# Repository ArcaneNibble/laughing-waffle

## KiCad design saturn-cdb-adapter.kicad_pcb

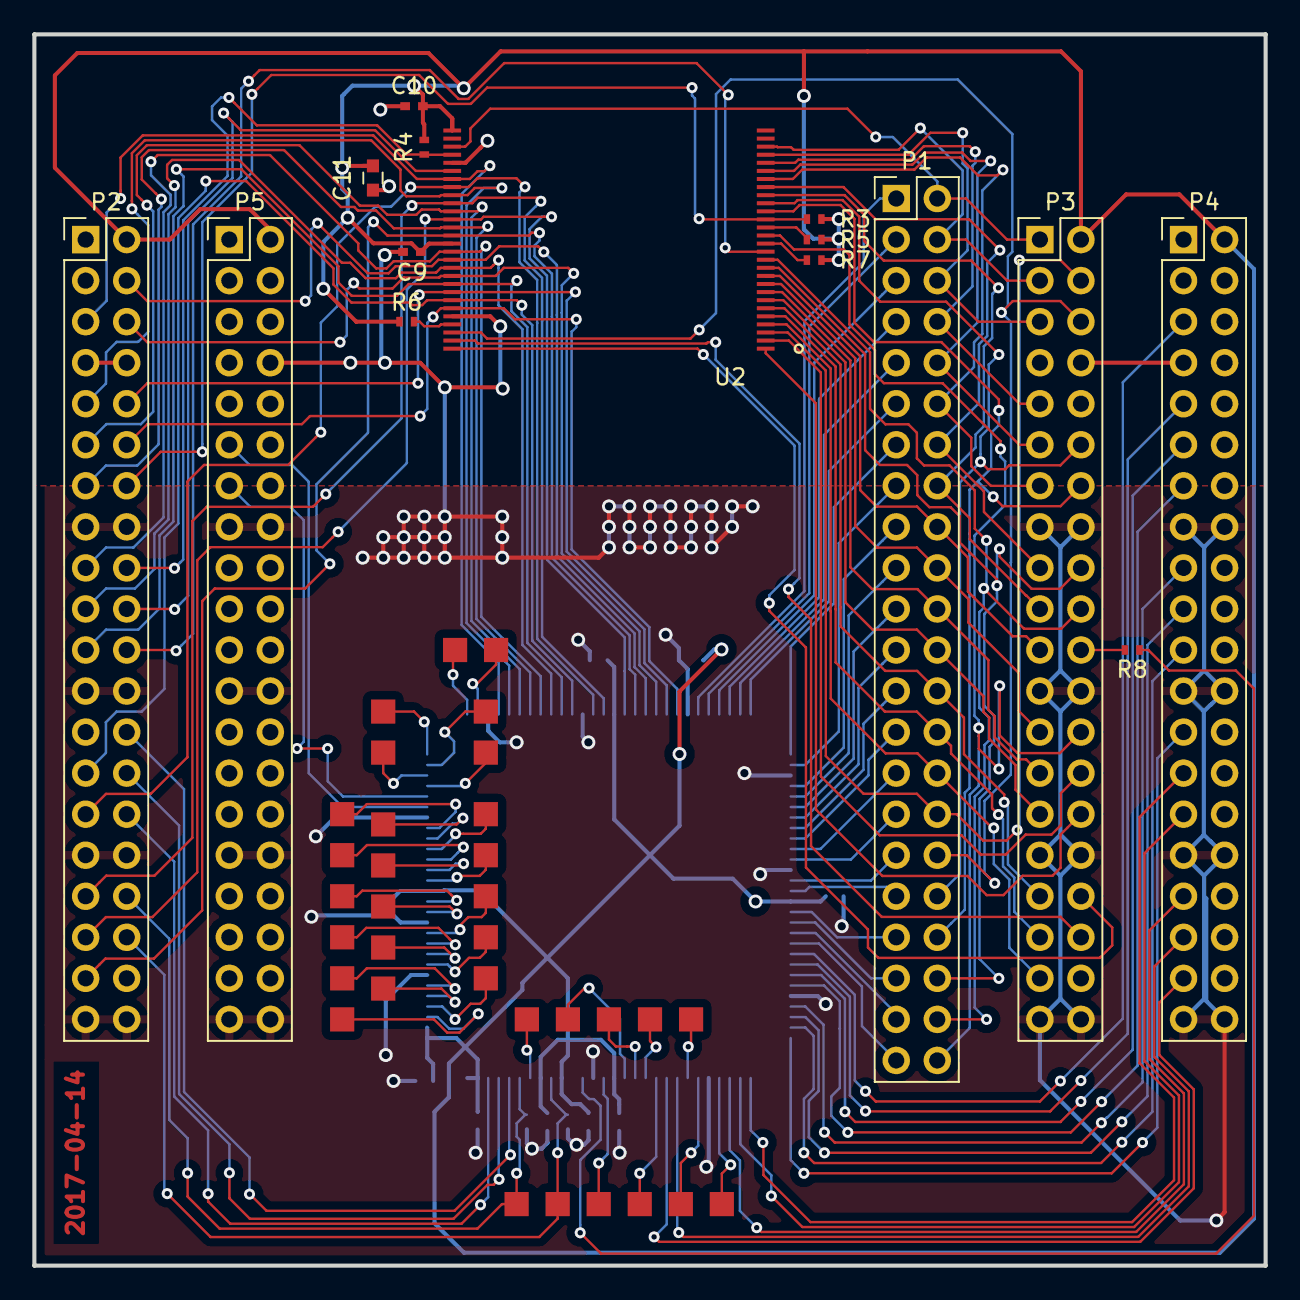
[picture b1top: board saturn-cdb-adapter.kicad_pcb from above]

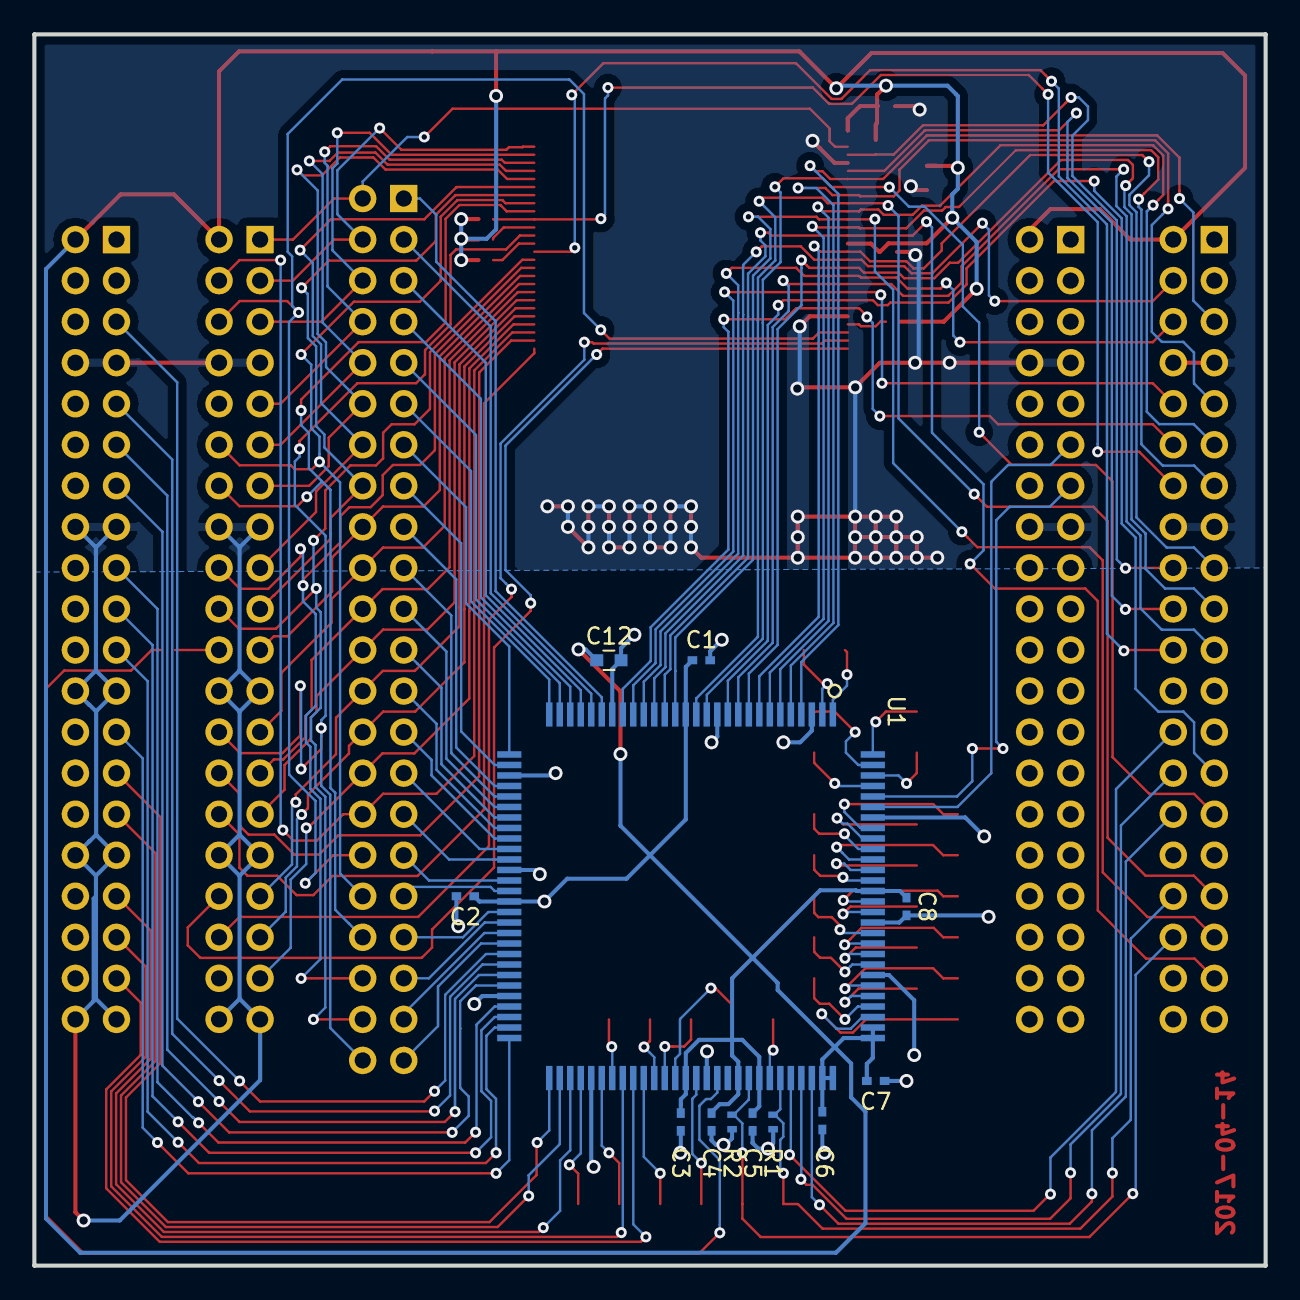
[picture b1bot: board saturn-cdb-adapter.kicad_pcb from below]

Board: 2 copper layers, 76.2 x 76.2 mm, 60 parts (12 on the bottom side), 126 nets.

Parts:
C1, C2, C3, C4, C5, C6, C7, C8, C9, C10: 0.1uF; C_0402_NoSilk
C11, C12: 1uF; C_0603
P1: CONN_02X22; Pin_Header_Straight_2x22_Pitch2.54mm
P2, P3, P4, P5: CONN_02X20; Pin_Header_Straight_2x20_Pitch2.54mm
R1, R2, R3, R4: 10k; R_0402_NoSilk
R5, R6, R7, R8: 0; R_0402_NoSilk
U1: SH1; cdb-sh1
U2: MT28EW_FLASH; TSOP56
W1, W2, W3, W4, W5, W6, W7, W8, W9, W10, W11, W12, W13, W14, W15, W16, W17, W18, W19, W20, W21, W22, W23, W24, W25, W26, W27, W28, W29, W30, W31, W32, W33: TEST_1P; Measurement_Point_Square-SMD-Pad_Small

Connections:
+3V3: C1.1, C2.1, C3.1, C4.1, C5.1, C6.1, C7.1, C8.1, C9.1, C10.1, C11.1, C12.1, P2.2, P3.2, P4.2, P5.2, R3.1, R4.1, R5.1, R6.1, R7.1, U1.15, U1.43, U1.70, U1.75, U1.77, U1.83, U1.84, U1.85, U1.86, U1.99, U2.29, U2.43
/Flash and CPU/CPU_A0: P1.1, U1.23
/Flash and CPU/CPU_A1: P1.3, U1.24
/Flash and CPU/CPU_A2: P1.5, U1.25
/Flash and CPU/CPU_A3: P1.7, U1.26
/Flash and CPU/CPU_A4: P1.9, U1.27
/Flash and CPU/CPU_A5: P1.11, U1.28
/Flash and CPU/CPU_A6: P1.13, U1.29
/Flash and CPU/CPU_A7: P1.15, U1.30
/Flash and CPU/CPU_A8: P1.17, U1.32
/Flash and CPU/CPU_A9: P1.19, U1.33
/Flash and CPU/CPU_A10: P1.21, U1.34
/Flash and CPU/CPU_A11: P1.23, U1.35
/Flash and CPU/CPU_A12: P1.25, U1.36
/Flash and CPU/CPU_A13: P1.27, U1.37
/Flash and CPU/CPU_A14: P1.29, U1.38
/Flash and CPU/CPU_A15: P1.31, U1.39
/Flash and CPU/CPU_A16: P1.33, U1.41
/Flash and CPU/CPU_A17: P1.35, U1.42
/Flash and CPU/CPU_A18: P1.37, U1.44
/Flash and CPU/CPU_A19: P1.39, U1.45
/Flash and CPU/CPU_A20: P1.41, U1.46
/Flash and CPU/CPU_A21: P1.43, U1.47
AD0: P2.5, U1.4, U2.35
AD1: P2.9, U1.5, U2.37
AD2: P2.11, U1.6, U2.39
AD3: P2.13, U1.7, U2.41
AD4: P2.17, U1.8, U2.44
AD5: P2.19, U1.9, U2.46
AD6: P2.21, U1.10, U2.48
AD7: P2.27, U1.11, U2.50
AD8: P2.29, U1.13, U2.36
AD9: P2.33, U1.14, U2.38
AD10: P2.35, U1.16, U2.40
AD11: P2.37, U1.17, U2.42
AD12: P2.4, U1.18, U2.45
AD13: P2.6, U1.19, U2.47
AD14: P2.10, U1.20, U2.49
AD15: P2.12, U1.21, U2.51
CPU_CLK: R8.1, U1.73
CPU_DPH: P4.37, U1.65
CPU_DPL: P4.35, U1.64
CPU_NMI: P2.36, R2.1, U1.76, W2.1
CPU_RX: P5.11, U1.107
CPU_TX: P5.13, U1.108
CPU_~CS0: P4.5, U1.48
CPU_~CS1: P4.9, U1.49
CPU_~CS2: P4.11, U1.50
CPU_~CS3: P4.13, U1.51
CPU_~CS4: P4.17, U1.53
CPU_~CS5: P4.19, U1.54
CPU_~CS6: P4.21, U1.55
CPU_~CS7: P4.25, U1.56
CPU_~RD: P4.33, U1.59
CPU_~RES: P2.34, R1.1, U1.79, W1.1
CPU_~WRH~/~LBS~: P4.29, U1.58
CPU_~WRL~/~WR: P4.27, U1.57
FLASH_A0: P1.2, P3.1, U2.31
FLASH_A1: P1.4, P3.3, U2.26
FLASH_A2: P1.6, P3.5, U2.25
FLASH_A3: P1.8, P3.9, U2.24
FLASH_A4: P1.10, P3.11, U2.23
FLASH_A5: P1.12, P3.13, U2.22
FLASH_A6: P1.14, P3.17, U2.21
FLASH_A7: P1.16, P3.19, U2.20
FLASH_A8: P1.18, P3.21, U2.10
FLASH_A9: P1.20, P3.25, U2.9
FLASH_A10: P1.22, P3.27, U2.8
FLASH_A11: P1.24, P3.29, U2.7
FLASH_A12: P1.26, P3.33, U2.6
FLASH_A13: P1.28, P3.35, U2.5
FLASH_A14: P1.30, P3.37, U2.4
FLASH_A15: P1.32, P3.4, U2.3
FLASH_A16: P1.34, P3.6, U2.54
FLASH_A17: P1.36, P3.12, U2.19
FLASH_A18: P1.38, P3.14, U2.18
FLASH_A19: P1.40, P3.18, U2.11
FLASH_A20: P1.42, P3.20, U2.12
FLASH_A21: P1.44, P3.26, U2.15
FLASH_A22: P3.28, U2.2
FLASH_A23: P3.30, U2.1
FLASH_A24: P3.34, U2.56
FLASH_A25: P3.36, U2.55
FLASH_READY: P2.14, R3.2, U2.17
GND: C1.2, C2.2, C3.2, C4.2, C5.2, C6.2, C7.2, C8.2, C9.2, C10.2, C11.2, C12.2, P2.7, P2.8, P2.15, P2.16, P2.23, P2.24, P2.31, P2.32, P2.39, P2.40, P3.7, P3.8, P3.15, P3.16, P3.23, P3.24, P3.31, P3.32, P3.39, P3.40, P4.7, P4.8, P4.15, P4.16, P4.23, P4.24, P4.31, P4.32, P4.39, P4.40, P5.7, P5.8, P5.15, P5.16, P5.23, P5.24, P5.31, P5.32, P5.39, P5.40, R1.2, R2.2, U1.3, U1.12, U1.22, U1.31, U1.40, U1.52, U1.61, U1.72, U1.91, U1.96, U1.106, U2.33, U2.52
MD0: P2.26, U1.80
MD1: P2.28, U1.81
MD2: P2.30, U1.82
unnamed: P3.22, R8.2
unnamed: R5.2, U2.16
unnamed: R6.2, U2.53
unnamed: R7.2, U2.14
unnamed: U1.1, W29.1
unnamed: U1.2, W14.1
unnamed: U1.60, W19.1
unnamed: U1.62, W5.1
unnamed: U1.63, W20.1
unnamed: U1.66, W6.1
unnamed: U1.67, W21.1
unnamed: U1.68, W7.1
unnamed: U1.69, W22.1
unnamed: U1.71, W3.1
unnamed: U1.78, W4.1
unnamed: U1.87, W30.1
unnamed: U1.88, W15.1
unnamed: U1.89, W31.1
unnamed: U1.90, W16.1
unnamed: U1.92, W32.1
unnamed: U1.93, W17.1
unnamed: U1.94, W33.1
unnamed: U1.95, W18.1
unnamed: U1.97, W8.1
unnamed: U1.98, W23.1
unnamed: U1.100, W9.1
unnamed: U1.101, W24.1
unnamed: U1.102, W10.1
unnamed: U1.103, W25.1
unnamed: U1.104, W11.1
unnamed: U1.105, W26.1
unnamed: U1.109, W27.1
unnamed: U1.110, W12.1
unnamed: U1.111, W28.1
unnamed: U1.112, W13.1
~FLASH_CE: P2.18, R4.2, U2.32
~FLASH_OE: P2.20, U2.34
~FLASH_WE: P2.22, U2.13

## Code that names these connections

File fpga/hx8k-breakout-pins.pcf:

set_io ad[0]    P16
set_io ad[1]    N16
set_io ad[2]    M16
set_io ad[3]    K15
set_io ad[4]    K14
set_io ad[5]    G14
set_io ad[6]    J15
set_io ad[7]    G16
set_io ad[8]    F16
set_io ad[9]    E16
set_io ad[10]   D16
set_io ad[11]   C16
set_io ad[12]   R15
set_io ad[13]   P15
set_io ad[14]   M15
set_io ad[15]   L16

set_io a[0]     R16
set_io a[1]     T15
set_io a[2]     T13
set_io a[3]     N12
set_io a[4]     N10
set_io a[5]     T11
set_io a[6]     T10
set_io a[7]     P8
set_io a[8]     T9
set_io a[9]     T7
set_io a[10]    T6
set_io a[11]    T5
set_io a[12]    R3
set_io a[13]    R2
set_io a[14]    T1
set_io a[15]    T16
set_io a[16]    T14
set_io a[17]    M11
set_io a[18]    P10
set_io a[19]    R10
set_io a[20]    P9
set_io a[21]    T8
set_io a[22]    R6
set_io a[23]    R5
set_io a[24]    R4
set_io a[25]    T3

set_io flash_ready      K16
set_io flash_nce        J14
set_io flash_noe        F14
set_io flash_nwe        H14


set_io md0          G15
set_io md1          F15
set_io md2          E14
set_io cpu_nres     D15
set_io cpu_nmi      D14
set_io cpu_clk      R9

set_io cpu_rx       A11
set_io cpu_tx       A10


set_io cpu_ncs[0]   P1
set_io cpu_ncs[1]   N3
set_io cpu_ncs[2]   M2
set_io cpu_ncs[3]   L3
set_io cpu_ncs[4]   K3
set_io cpu_ncs[5]   J2
set_io cpu_ncs[6]   H2
set_io cpu_ncs[7]   G2

set_io cpu_nwrl_nwr     F2
set_io cpu_nwrh_nlbs    E2
set_io cpu_nrd          D1
set_io cpu_dpl          C1
set_io cpu_dph          B1


set_io led[0]   B5
set_io led[1]   B4
set_io led[2]   A2
set_io led[3]   A1
set_io led[4]   C5
set_io led[5]   C4
set_io led[6]   B3
set_io led[7]   C3

set_io ftdi_tx      B12
set_io ftdi_rx      B10

set_io ftdi_rts     B13
set_io ftdi_dtr     A16

set_io clk_12mhz    J3

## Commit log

2017-04-13 Import initial work into git
2017-04-13 Add fp-lib-table file
2017-04-13 Split design into heirarchical sheets
2017-04-13 Change to use US Letter size
2017-04-13 Added a gitignore
2017-04-13 Initial working? version
2017-04-13 Add global nets correctly and annotate
2017-04-14 Rough initial placement and fix sh1 footprint
2017-04-14 Fix sh1 footprint some more
2017-04-14 More minor adjustments
2017-04-14 Initial very rough route for most signals
2017-04-14 Initial all signals connected
2017-04-14 SH power into star; minor cleanup
2017-04-15 Trace cleanup
2017-04-15 Optimize more other than power
2017-04-15 Optimize power a bit
2017-04-15 Silkscreen and fab notes fixes
2017-04-15 Final OCD fixes
2017-04-15 Add gerbers for rev A
2017-05-15 Initial FPGA code
2017-05-15 Instantiate PLL
2017-05-15 Instantiate uart
2017-05-15 Loopback works
2017-05-16 Flash R/W works
2017-05-16 Start working on dumper tool
2017-05-17 Stuff doesn't quite work, but can R/W from FPGA
2017-05-17 Can get bytes back
2017-05-17 Dumping seems to work!
